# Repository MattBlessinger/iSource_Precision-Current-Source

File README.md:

# Precision-Current-Source
Low-cost precision current source for calibrating multimeters, ammeters, current shunts, etc.

### Overview
The current source is based on an electronic load in which an op amp sets a known voltage drop across precision resistors. To maintain accuracy, the set-point voltage is constant and sourced by the MAX6070 low-noise, high-precision voltage reference. Different currents are selected by changing the shunt resistors with a pin header jumper. The initial accuracy without tuning (determined by detailed calculations) is <0.1% for 500mA, <0.1% for currents of 50mA to 500nA, <0.2% for 50nA, and <0.5% for 10nA. The measured accuracy was found to be within the expected values except for the nA ranges, likely due to measurement error (see the results spreadsheet file).

### Usage
To use the current source, connect the device under test (DUT) (multimeter, etc.) to the Output +/- 4mm banana connectors on the iSource. (This setup is high-side current sensing.) Put the current set and sense jumpers in the desired position; note that the bottom sense position applies to the set currents of 1.25mA and below. Connect power leads to the screw terminal block and apply power. The current set and sense jumpers can be changed while power is applied without harming the iSource.

### Design
The electronic load design is well-known amongst the electronics community. A commonly referenced design is "EEVBlog 102 – DIY Constant Current Dummy Load for Power Supply and Battery Test." In short, the op amp controls the mosfet's gate voltage to vary the voltage drop across shunt resistors between the mosfet source and ground. The voltage drop is fed to the inverting input of the op amp to provide closed-loop feedback. The set point voltage is routed to the non-inverting input of the op amp. The difference from an electronic load is that the set point voltage does not vary, instead it is constant and supplied by a precision voltage reference. To change the current, the shunt resistors are changed. The DUT is wired between Vdd and the mosfet drain.

The current ranges were chosen based on my initial desire to calibrate my 6000 count multimeter and the EEVBlog uCurrent, hence the 50, 500 and 1250 values. The ranges can be changed by using different resistor combinations. The banana jacks are spaced at the industry standard 0.75". The power input is labeled as 5V but can work down to 4V, e.g. Li-Ion cell. Pin headers and jumpers were used to select the current ranges since low-leakage JFETs can't handle the higher current ranges, and dip switches can't switch the higher either. A parallel load was added to impose a minimum 3mA current through the mosfet to eliminate leakage current issues in the nA ranges. Separate sense pins are used for the 50 and 500mA ranges to account for voltage drop along the tracks due to the higher current. (Voltage drop along the tracks are included in the accuracy calculations for all current ranges.) A DPAK mosfet was used in order to use a heatsink since the mosfet will dissipate a fair amount of heat at 500mA range. It is desired to take the heat away from the PCB in order to not heat the resistors, op amp and voltage reference.

The component choices typically came down to accuracy and cost. The voltage reference gives 0.04% initial accuracy and low thermal drift for $3.35 in one off quantities. The op amp has low input offset voltage (8uV), low input offset current (5pA), and low gain-bandwidth product (80kHz) to prevent the common ringing problem, all for $1.15 in one off quantities. The highest precision resistors were used for a each current range, so cost was minimized by the selection of resistor combinations.

### Accuracy
Several steps were taken to account for the current-induced voltage drop along tracks. As previously mentioned separate sense pins are used for 50 and 500mA so that separate tracks are run to the net-zero middle of the resistor pack. The op amp's ground is run to the net-zero middle of 500mA resistor ground pack since it has the greatest voltage drop. A large ground pour is used to minimuze the resistance between the ground of the op amp and rest of the current ranges' ground return.

Extensive calculations were performed to determine the maximum guaranteed tolerance for an as-built unit. (I did not want to rely on tuning each current range.) The calculations assume worst case scenario for all specifications provided in data sheets, thus the numbers ought to be maximum accuracy values. The parameters included in the accuracy calculations are:
* **Voltage reference**: initial accuracy, thermal drift, thermal hysteresis
* **Resistors**: tolerance, thermal coefficient
* **Op amp**: offset voltage, input bias current, input offset current
* **Track resistance**: resistance from sense pin to first resistor, resistance from last resistor to voltage reference ground, optimized track routing of high-current settings

### Results
I measured the accuracy with a Keysight 34465A 6.5 digit DMM with a 4 month old calibration. The 34465A has a low current range of 1uA with 1pA resolution. I used a single cell lithium ion battery charged to 4.2V to power the iSource. I placed the battery and iSource in a cast aluminum case to minimize EMI. The output was wired to the 34465A with an unshielded twisted pair wires. I used remote logging via PyVISA to remove myself from the measurement area. The 34465A was warmed up for 1 hour, and each current range was allowed to settle for 5 minutes before collecting data, although the currents settled within 10-30 seconds. I took 500 measurements with 10 NPLC at the lowest 34465A current range possible.

The spreadsheet shows the average value, accuracy % based on the measured average, 34465A uncertainty, and standard deviation of the 500 measurements. I suspect the increased inaccuracy of nA ranges is due to my measurement setup as I do not know all the proper techniques nor have the proper setup for them.

### Cost
As of June, 2017, the total build cost was $48 including the OSHPark PCB not listed in the BOM. Lower tolerance resistors may be used to significantly reduce the cost. New accuracy calculations can be performed by changing the resistor tolerance in the spreadsheet.

### License
The project is licensed as open source hardware and Creative Commons Attribution-ShareAlike 3.0 (CC BY-SA 3.0 US)

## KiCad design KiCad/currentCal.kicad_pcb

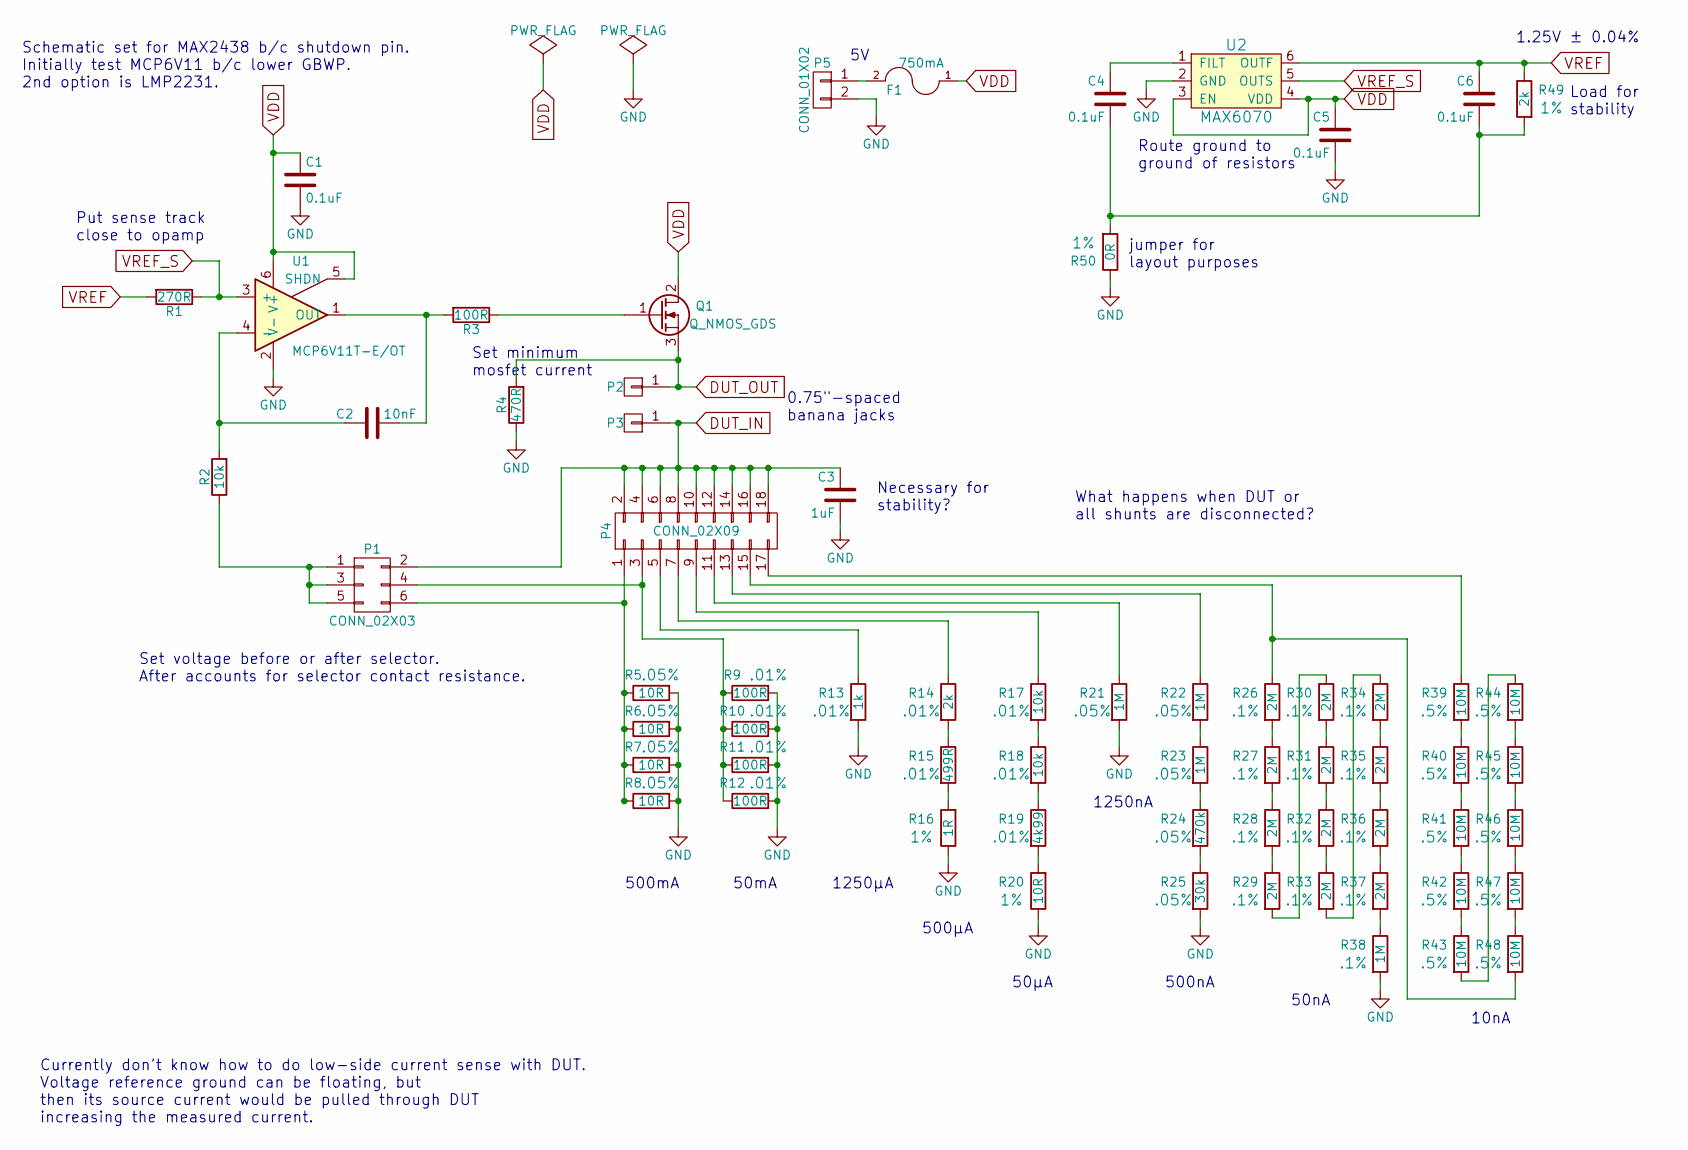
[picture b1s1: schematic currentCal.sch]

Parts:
C1, C4, C5, C6: 0.1uF; C_0603
C2: 10nF; C_0603
C3: 1uF; C_0603
F1: 750mA; FUSE_0603
P1: CONN_02X03; Pin_Header_Straight_2x03
P2, P3: CONN_01X01; Binding_post_4mm
P4: CONN_02X09; Pin_Header_Straight_2x09
P5: CONN_01X02; TerminalBlock_Pheonix_MKDS1.5-2pol_1985849
Q1: Q_NMOS_GDS; TO-252_wHeatsink
R1: 270R; R_0603
R2: 10k; R_0603
R3: 100R; R_0603
R4: 470R; R_0805
R5, R6, R7, R8: 10R; R_1206; Tolerance .05%
R9, R10, R11, R12: 100R; R_0603; Tolerance .01%
R13: 1k; R_0805; Tolerance .01%
R14: 2k; R_1206; Tolerance .01%
R15: 499R; R_0805; Tolerance .01%
R16: 1R; R_0603; Tolerance 1%
R17, R18: 10k; R_0603; Tolerance .01%
R19: 4k99; R_0603; Tolerance .01%
R20: 10R; R_0603; Tolerance 1%
R21, R22, R23: 1M; R_1206; Tolerance .05%
R24: 470k; R_0805; Tolerance .05%
R25: 30k; R_0603; Tolerance .05%
R26, R27, R28, R29, R30, R31, R32, R33, R34, R35, R36, R37: 2M; R_0805; Tolerance .1%
R38: 1M; R_0805; Tolerance .1%
R39, R40, R41, R42, R43, R44, R45, R46, R47, R48: 10M; R_0603; Tolerance .5%
R49: 2k; R_0603; Tolerance 1%
R50: 0R; R_0603; Tolerance 1%
U1: MCP6V11T-E/OT; SOT-23-6
U2: MAX6070; SOT-23-6

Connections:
DUT_IN: C3.1, P1.2, P3.1, P4.2, P4.4, P4.6, P4.8, P4.10, P4.12, P4.14, P4.16, P4.18
DUT_OUT: P2.1, Q1.3 (S), R4.2
GND: C1.2, C3.2, C5.2, P5.2, R4.1, R5.2, R6.2, R7.2, R8.2, R9.2, R10.2, R11.2, R12.2, R13.2, R16.1, R20.1, R21.2, R25.2, R38.2, R50.1, U1.2 (V-), U2.2 (GND)
unnamed: C2.1, R2.2, U1.4 (-)
unnamed: C2.2, R3.2, U1.1 (OUT)
unnamed: C4.1, U2.1 (FILT)
unnamed: C4.2, C6.2, R49.2, R50.2
unnamed: F1.2, P5.1
unnamed: P1.1, P1.3, P1.5, R2.1
unnamed: P1.4, P4.3, R9.1, R10.1, R11.1, R12.1
unnamed: P1.6, P4.1, R5.1, R6.1, R7.1, R8.1
unnamed: P4.5, R13.1
unnamed: P4.7, R14.1
unnamed: P4.9, R17.1
unnamed: P4.11, R21.1
unnamed: P4.13, R22.1
unnamed: P4.15, R26.1, R48.2
unnamed: P4.17, R39.1
unnamed: Q1.1 (G), R3.1
unnamed: R14.2, R15.1
unnamed: R15.2, R16.2
unnamed: R17.2, R18.1
unnamed: R18.2, R19.1
unnamed: R19.2, R20.2
unnamed: R22.2, R23.1
unnamed: R23.2, R24.1
unnamed: R24.2, R25.1
unnamed: R26.2, R27.1
unnamed: R27.2, R28.1
unnamed: R28.2, R29.1
unnamed: R29.2, R30.1
unnamed: R30.2, R31.1
unnamed: R31.2, R32.1
unnamed: R32.2, R33.1
unnamed: R33.2, R34.1
unnamed: R34.2, R35.1
unnamed: R35.2, R36.1
unnamed: R36.2, R37.1
unnamed: R37.2, R38.1
unnamed: R39.2, R40.1
unnamed: R40.2, R41.1
unnamed: R41.2, R42.1
unnamed: R42.2, R43.1
unnamed: R43.2, R44.1
unnamed: R44.2, R45.1
unnamed: R45.2, R46.1
unnamed: R46.2, R47.1
unnamed: R47.2, R48.1
VDD: C1.1, C5.1, F1.1, Q1.2 (D), U1.5 (SHDN), U1.6 (V+), U2.3 (EN), U2.4 (VDD)
VREF: C6.1, R1.2, R49.1, U2.6 (OUTF)
VREF_S: R1.1, U1.3 (+), U2.5 (OUTS)

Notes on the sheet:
Currently don't know how to do low-side current sense with DUT. Voltage reference ground can be floating, but then its source current would be pulled through DUT increasing the measured current.
Set voltage before or after selector. After accounts for selector contact resistance.
Put sense track close to opamp
Load for stability
1.25V ± 0.04%
Route ground to ground of resistors
0.75"-spaced banana jacks
What happens when DUT or all shunts are disconnected?
Set minimum mosfet current
Schematic set for MAX2438 b/c shutdown pin. Initially test MCP6V11 b/c lower GBWP. 2nd option is LMP2231.
Necessary for stability?
500mA
50mA
1250µA
500µA
50µA
1250nA
500nA
50nA
10nA
jumper for layout purposes

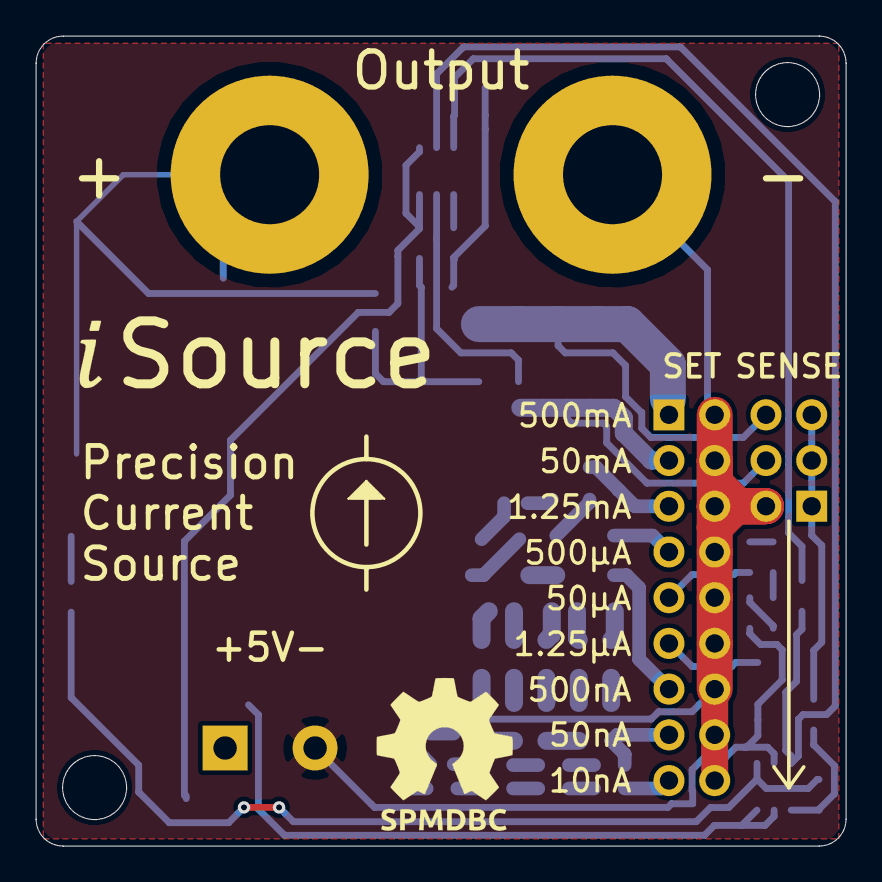
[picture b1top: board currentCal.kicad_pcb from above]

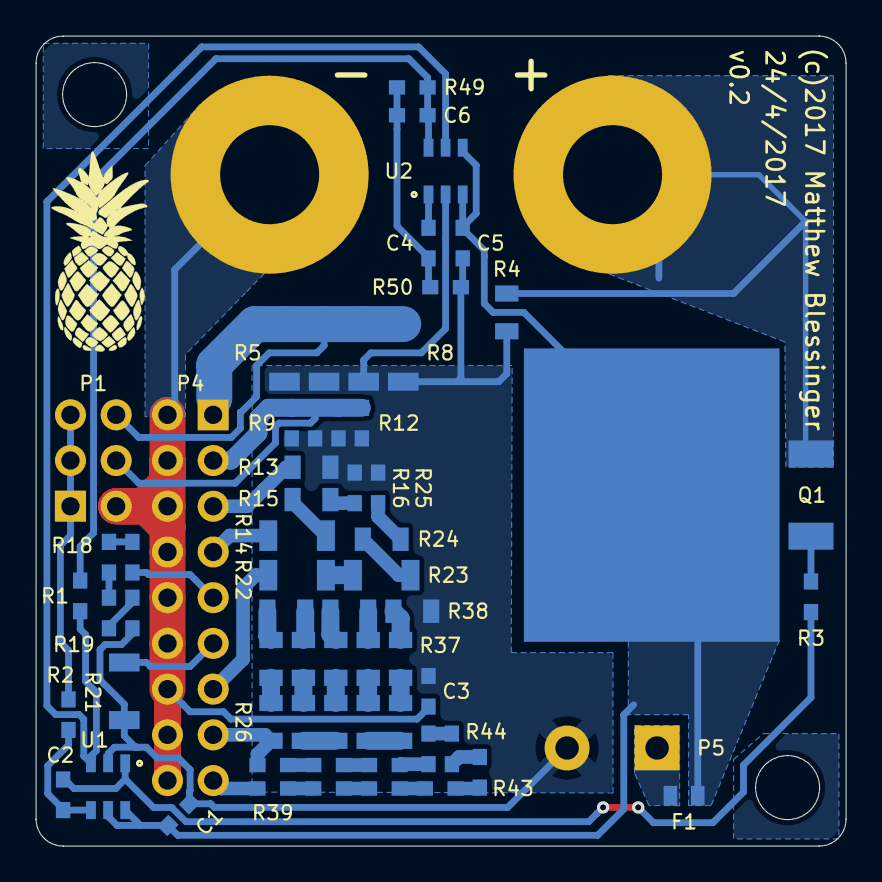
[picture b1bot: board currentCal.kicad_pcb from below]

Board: 2 copper layers, 45.0 x 45.0 mm, 65 parts (60 on the bottom side), 51 nets.

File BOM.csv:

Reference, Value, Footprint, Datasheet, Product ID, Manufacturer, ToleranceC1,0.1uF,MKB:C_0603,,GCM188R71H104KA57D,Murata, C5,0.1uF,MKB:C_0603,,GCM188R71H104KA57D,Murata, C6,0.1uF,MKB:C_0603,,GCM188R71H104KA57D,Murata, C4,0.1uF,MKB:C_0603,,GCM188R71H104KA57D,Murata, R50,0R,MKB:R_0603,,RC0603FR-072KL,Yageo,1%R9,100R,MKB:R_0603,,APC0603T100RZ,Ohmite,0.01%R10,100R,MKB:R_0603,,APC0603T100RZ,Ohmite,0.01%R11,100R,MKB:R_0603,,APC0603T100RZ,Ohmite,0.01%R12,100R,MKB:R_0603,,APC0603T100RZ,Ohmite,0.01%R3,100R,MKB:R_0603,,RC0603FR-07100RL,Yageo, R17,10k,MKB:R_0603,,APC0603T10K0Z,Ohmite,0.01%R18,10k,MKB:R_0603,,APC0603T10K0Z,Ohmite,0.01%R2,10k,MKB:R_0603,,RC0603FR-0710KL,Yageo, R39,10M,MKB:R_0603,,CRCW060310M0DHEAP,Vishay Dale,0.50%R40,10M,MKB:R_0603,,CRCW060310M0DHEAP,Vishay Dale,0.50%R41,10M,MKB:R_0603,,CRCW060310M0DHEAP,Vishay Dale,0.50%R42,10M,MKB:R_0603,,CRCW060310M0DHEAP,Vishay Dale,0.50%R43,10M,MKB:R_0603,,CRCW060310M0DHEAP,Vishay Dale,0.50%R44,10M,MKB:R_0603,,CRCW060310M0DHEAP,Vishay Dale,0.50%R45,10M,MKB:R_0603,,CRCW060310M0DHEAP,Vishay Dale,0.50%R46,10M,MKB:R_0603,,CRCW060310M0DHEAP,Vishay Dale,0.50%R47,10M,MKB:R_0603,,CRCW060310M0DHEAP,Vishay Dale,0.50%R48,10M,MKB:R_0603,,CRCW060310M0DHEAP,Vishay Dale,0.50%C2,10nF,MKB:C_0603,,GRM188R71H103JA01D,Murata, R20,10R,MKB:R_0603,,RC0603FR-0710RL,Yageo,1%R5,10R,MKB:R_1206,,RNCF1206AKT10R0,Stackpole Electronics,0.05%R6,10R,MKB:R_1206,,RNCF1206AKT10R0,Stackpole Electronics,0.05%R7,10R,MKB:R_1206,,RNCF1206AKT10R0,Stackpole Electronics,0.05%R8,10R,MKB:R_1206,,RNCF1206AKT10R0,Stackpole Electronics,0.05%R13,1k,MKB:R_0805,,APC0805T1K00Z,Ohmite,0.01%R38,1M,MKB:R_0805,,CPF0805B1M0E1,TE Connectivity,0.10%R21,1M,MKB:R_1206,,RG3216N-1004-W-T1,Susumu,0.05%R22,1M,MKB:R_1206,,RG3216N-1004-W-T1,Susumu,0.05%R23,1M,MKB:R_1206,,RG3216N-1004-W-T1,Susumu,0.05%R16,1R,MKB:R_0603,,RC0603FR-071RL,Yageo,1%C3,1uF,MKB:C_0603,,GCM188R71H104KA57D,Murata, R1,270R,MKB:R_0603,,RC0603FR-07270RL,Yageo, R14,2k,MKB:R_1206,,APC1206T2K00Z,Ohmite,0.01%R49,2k,MKB:R_0603,,RC0603FR-072KL,Yageo,1%R26,2M,MKB:R_0805,,CPF0805B2M0E1,TE Connectivity,0.10%R27,2M,MKB:R_0805,,CPF0805B2M0E1,TE Connectivity,0.10%R28,2M,MKB:R_0805,,CPF0805B2M0E1,TE Connectivity,0.10%R29,2M,MKB:R_0805,,CPF0805B2M0E1,TE Connectivity,0.10%R30,2M,MKB:R_0805,,CPF0805B2M0E1,TE Connectivity,0.10%R31,2M,MKB:R_0805,,CPF0805B2M0E1,TE Connectivity,0.10%R32,2M,MKB:R_0805,,CPF0805B2M0E1,TE Connectivity,0.10%R33,2M,MKB:R_0805,,CPF0805B2M0E1,TE Connectivity,0.10%R34,2M,MKB:R_0805,,CPF0805B2M0E1,TE Connectivity,0.10%R35,2M,MKB:R_0805,,CPF0805B2M0E1,TE Connectivity,0.10%R36,2M,MKB:R_0805,,CPF0805B2M0E1,TE Connectivity,0.10%R37,2M,MKB:R_0805,,CPF0805B2M0E1,TE Connectivity,0.10%R25,30k,MKB:R_0603,,RG1608N-303-W-T1,Susumu,0.05%R24,470k,MKB:R_0805,,RG2012N-474-W-T1,Susumu,0.05%R4,470R,MKB:R_0805,,RC0805FR-07470RL,Yageo, R15,499R,MKB:R_0805,,APC0805T499RZ,Ohmite,0.01%R19,4k99,MKB:R_0603,,APC0603T4K99Z,Ohmite,0.01%F1,750mA,MKB:FUSE_0603,,C2Q 750,Bel Fuse, P2,CONN_01X01,MKB:Binding_post_4mm,,_,_, P3,CONN_01X01,MKB:Binding_post_4mm,,_,_, P5,CONN_01X02,MKB:TerminalBlock_Pheonix_MKDS1.5-2pol_1985849,,1985849,Phoenix Contact,P1,CONN_02X03,Pin_Headers:Pin_Header_Straight_2x03,,,,P4,CONN_02X09,Pin_Headers:Pin_Header_Straight_2x09,,,,U2,MAX6070,MKB:SOT-23-6,,MAX6070AAUT12+T,Maxim Integrated, U1,MCP6V11T-E/OT,MKB:SOT-23-6,,MCP6V11T-E/OT,Microchip, Q1,Q_NMOS_GDS,MKB:TO-252_wHeatsink,,BUK92150-55A_118,Nexperia,

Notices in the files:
KiCad/currentCal.kicad_pcb:
(c)2017 Matthew Blessinger
